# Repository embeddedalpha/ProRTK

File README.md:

# ProRTK 
Real Time Kinematic Board

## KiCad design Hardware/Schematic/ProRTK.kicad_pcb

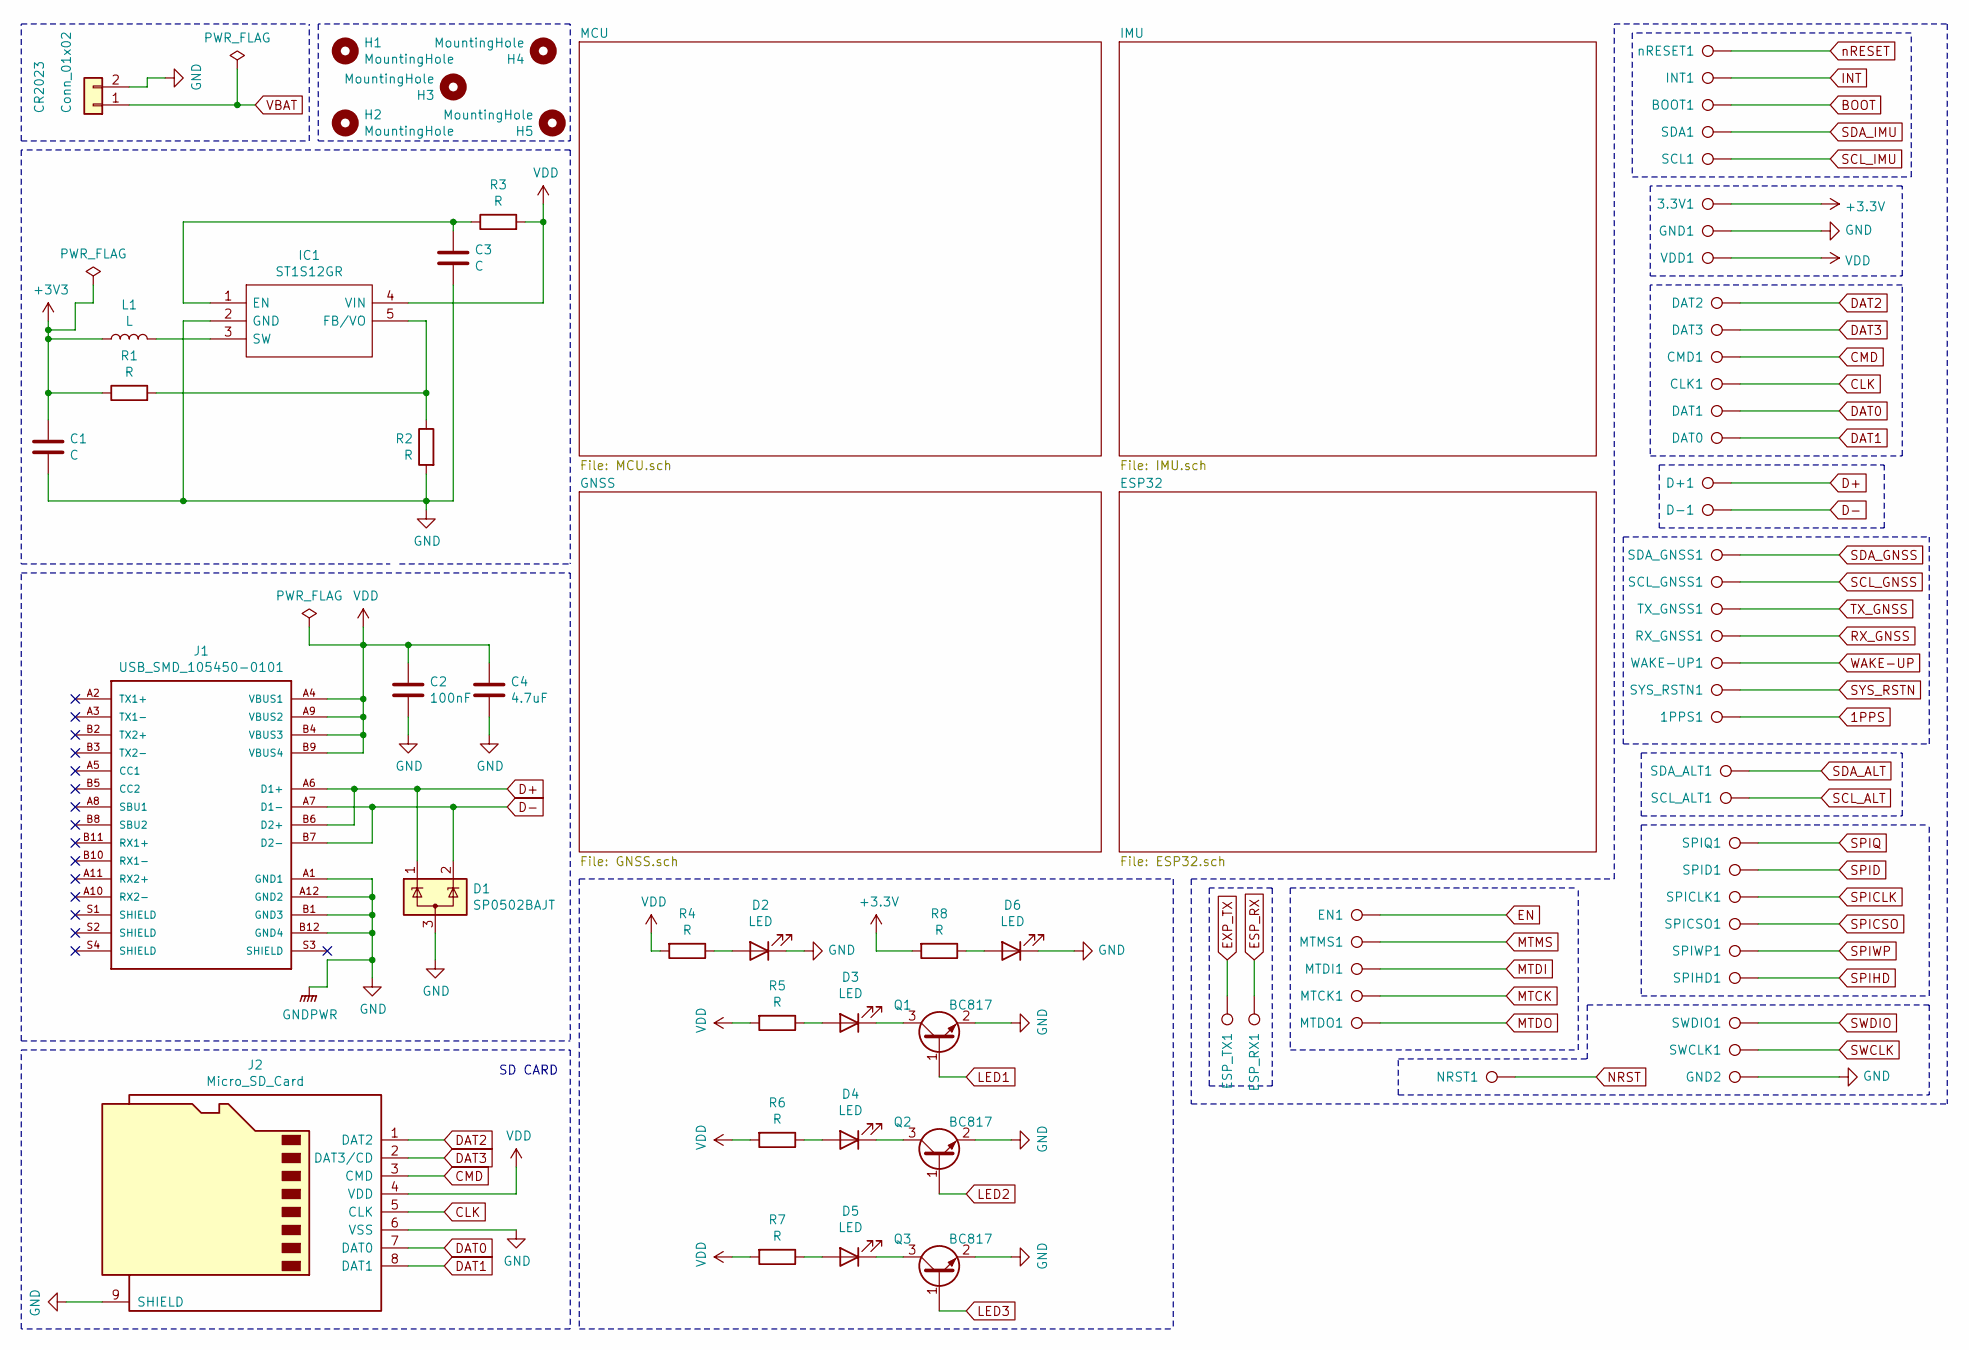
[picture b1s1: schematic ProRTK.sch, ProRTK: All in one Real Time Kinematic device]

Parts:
1PPS1, 3.3V1: TestPoint; testpoint_0.3mm
BOOT1: TestPoint; testpoint_0.3mm
C1, C3: C; C_0402_1005Metric
C2: 100nF; C_0402_1005Metric
C4: 4.7uF; C_0402_1005Metric
CLK1: TestPoint; testpoint_0.3mm
CMD1: TestPoint; testpoint_0.3mm
CR2023: Conn_01x02; BatteryHolder_Keystone_3034_1x20mm
D1: SP0502BAJT; SOT-323_SC-70
D2, D3, D4, D5, D6: LED; LED_0603_1608Metric
D+1: TestPoint; testpoint_0.3mm
D-1: TestPoint; testpoint_0.3mm
DAT0, DAT1, DAT2, DAT3: TestPoint; testpoint_0.3mm
EN1: TestPoint; testpoint_0.3mm
ESP_RX1: TestPoint; testpoint_0.3mm
ESP_TX1: TestPoint; testpoint_0.3mm
GND1, GND2: TestPoint; testpoint_0.3mm
H1, H2, H3, H4, H5: MountingHole; MountingHole_3.2mm_M3_Pad_Via
IC1: ST1S12GR; SOT95P280X110-5N; Mouser Part Number 511-ST1S12GR
INT1: TestPoint; testpoint_0.3mm
J1: USB_SMD_105450-0101; MOLEX_105450-0101
J2: Micro_SD_Card; microSD_HC_Hirose_DM3D-SF
L1: L; L_0402_1005Metric
MTCK1: TestPoint; testpoint_0.3mm
MTDI1: TestPoint; testpoint_0.3mm
MTDO1: TestPoint; testpoint_0.3mm
MTMS1: TestPoint; testpoint_0.3mm
NRST1: TestPoint; testpoint_0.3mm
Q1, Q2, Q3: BC817; SOT-23
R1, R2, R3, R4, R5, R6, R7, R8: R; R_0402_1005Metric
RX_GNSS1: TestPoint; testpoint_0.3mm
SCL1: TestPoint; testpoint_0.3mm
SCL_ALT1: TestPoint; testpoint_0.3mm
SCL_GNSS1: TestPoint; testpoint_0.3mm
SDA1: TestPoint; testpoint_0.3mm
SDA_ALT1: TestPoint; testpoint_0.3mm
SDA_GNSS1: TestPoint; testpoint_0.3mm
SPICLK1: TestPoint; testpoint_0.3mm
SPICSO1: TestPoint; testpoint_0.3mm
SPID1: TestPoint; testpoint_0.3mm
SPIHD1: TestPoint; testpoint_0.3mm
SPIQ1: TestPoint; testpoint_0.3mm
SPIWP1: TestPoint; testpoint_0.3mm
SWCLK1: TestPoint; testpoint_0.3mm
SWDIO1: TestPoint; testpoint_0.3mm
SYS_RSTN1: TestPoint; testpoint_0.3mm
TX_GNSS1: TestPoint; testpoint_0.3mm
VDD1: TestPoint; testpoint_0.3mm
WAKE-UP1: TestPoint; testpoint_0.3mm
nRESET1: TestPoint; testpoint_0.3mm

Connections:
1PPS: 1PPS1.1; also elsewhere on the board
BOOT: BOOT1.1; also elsewhere on the board
CLK: CLK1.1, J2.5 (CLK); also elsewhere on the board
CMD: CMD1.1, J2.3 (CMD); also elsewhere on the board
D+: D1.1 (K), D+1.1, J1.A6 (D1+), J1.B6 (D2+); also elsewhere on the board
D-: D1.2 (K), D-1.1, J1.A7 (D1-), J1.B7 (D2-); also elsewhere on the board
DAT0: DAT1.1, J2.7 (DAT0); also elsewhere on the board
DAT1: DAT0.1, J2.8 (DAT1); also elsewhere on the board
DAT2: DAT2.1, J2.1 (DAT2); also elsewhere on the board
DAT3: DAT3.1, J2.2 (DAT3/CD); also elsewhere on the board
EN: EN1.1; also elsewhere on the board
ESP_RX: ESP_RX1.1; also elsewhere on the board
EXP_TX: ESP_TX1.1; also elsewhere on the board
GND: C1.2, C2.2, C3.2, C4.2, CR2023.2, D1.3 (A), D2.1 (K), D6.1 (K), GND1.1, GND2.1, IC1.2 (GND), J1.A1 (GND1), J1.A12 (GND2), J1.B1 (GND3), J1.B12 (GND4), J2.6 (VSS), J2.9 (SHIELD), Q1.2 (E), Q2.2 (E), Q3.2 (E), R2.2; also elsewhere on the board
INT: INT1.1; also elsewhere on the board
LED1: Q1.1 (B); also elsewhere on the board
LED2: Q2.1 (B); also elsewhere on the board
LED3: Q3.1 (B); also elsewhere on the board
MTCK: MTCK1.1; also elsewhere on the board
MTDI: MTDI1.1; also elsewhere on the board
MTDO: MTDO1.1; also elsewhere on the board
MTMS: MTMS1.1; also elsewhere on the board
NRST: NRST1.1; also elsewhere on the board
unnamed: C3.1, IC1.1 (EN), R3.1
unnamed: D2.2 (A), R4.1
unnamed: D3.1 (K), Q1.3 (C)
unnamed: D3.2 (A), R5.1
unnamed: D4.1 (K), Q2.3 (C)
unnamed: D4.2 (A), R6.1
unnamed: D5.1 (K), Q3.3 (C)
unnamed: D5.2 (A), R7.1
unnamed: D6.2 (A), R8.1
unnamed: IC1.3 (SW), L1.2
unnamed: IC1.5 (FB/VO), R1.2, R2.1
RX_GNSS: RX_GNSS1.1; also elsewhere on the board
SCL_ALT: SCL1.1, SCL_ALT1.1; also elsewhere on the board
SCL_GNSS: SCL_GNSS1.1; also elsewhere on the board
SDA_ALT: SDA1.1, SDA_ALT1.1; also elsewhere on the board
SDA_GNSS: SDA_GNSS1.1; also elsewhere on the board
SPICLK: SPICLK1.1; also elsewhere on the board
SPICSO: SPICSO1.1; also elsewhere on the board
SPID: SPID1.1; also elsewhere on the board
SPIHD: SPIHD1.1; also elsewhere on the board
SPIQ: SPIQ1.1; also elsewhere on the board
SPIWP: SPIWP1.1; also elsewhere on the board
SWCLK: SWCLK1.1; also elsewhere on the board
SWDIO: SWDIO1.1; also elsewhere on the board
SYS_RSTN: SYS_RSTN1.1; also elsewhere on the board
TX_GNSS: TX_GNSS1.1; also elsewhere on the board
WAKE-UP: WAKE-UP1.1; also elsewhere on the board
nRESET: nRESET1.1; also elsewhere on the board

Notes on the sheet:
SD CARD

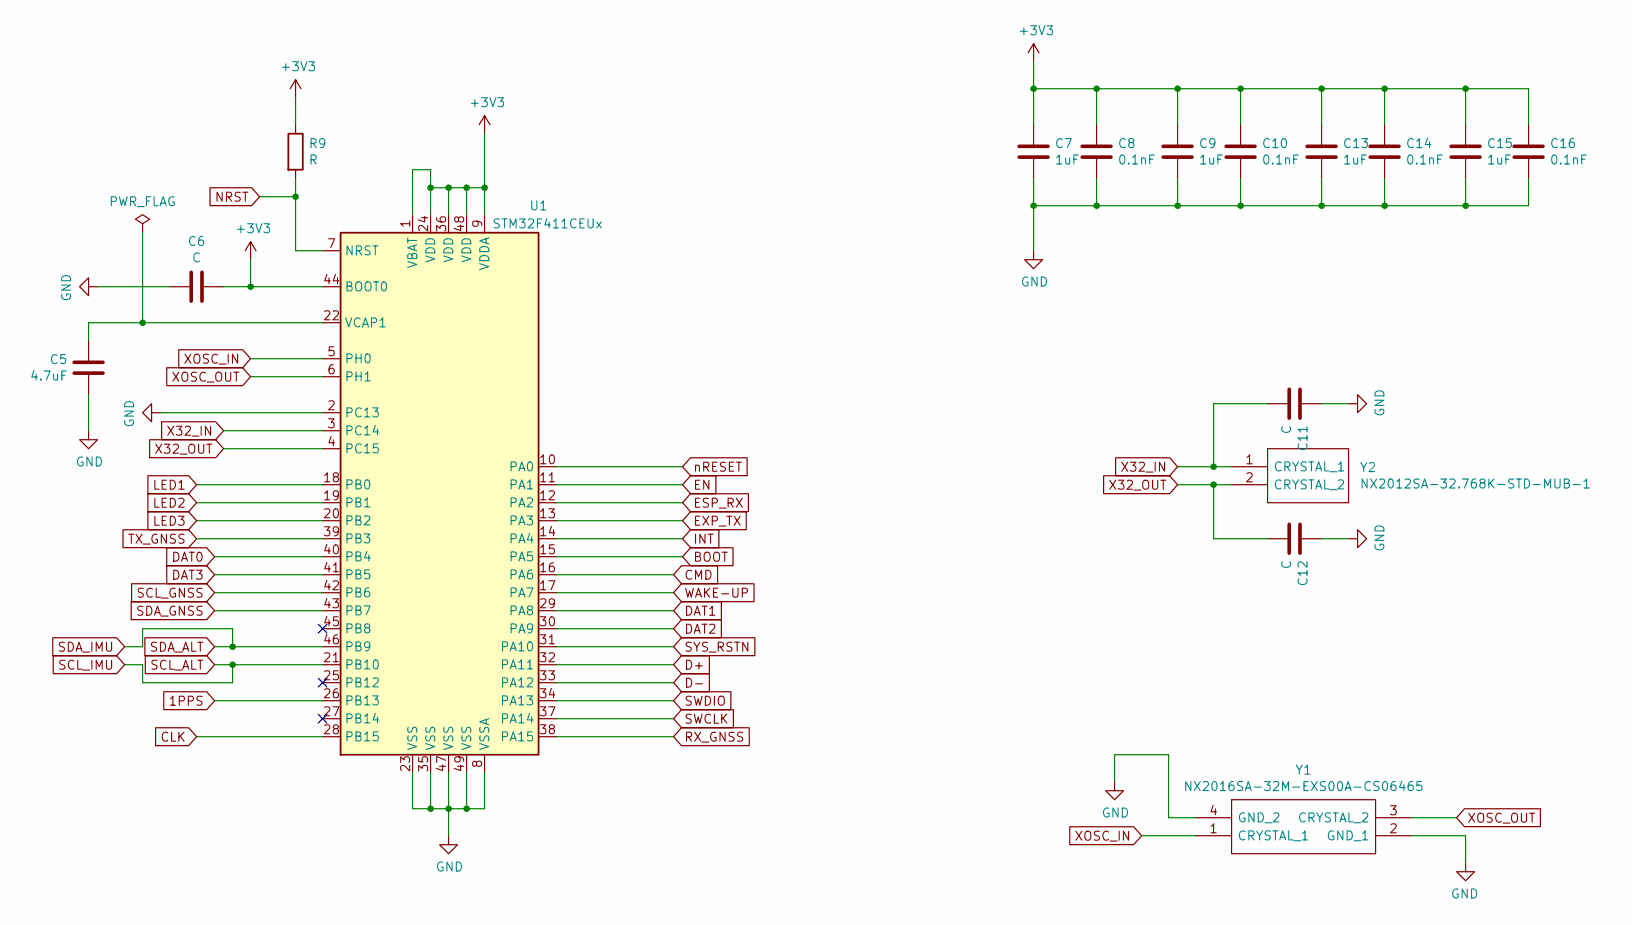
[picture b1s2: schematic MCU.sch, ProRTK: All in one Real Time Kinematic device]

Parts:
C5: 4.7uF; C_0402_1005Metric
C6, C11, C12: C; C_0402_1005Metric
C7, C9, C13, C15: 1uF; C_0402_1005Metric
C8, C10, C14, C16: 0.1nF; C_0402_1005Metric
R9: R; R_0402_1005Metric
U1: STM32F411CEUx; QFN-48-1EP_7x7mm_P0.5mm_EP5.6x5.6mm
Y1: NX2016SA-32M-EXS00A-CS06465; NX2016SA32MEXS00ACS06465; Mouser Part Number 344-NX2016SA32S06465
Y2: NX2012SA-32.768K-STD-MUB-1; NX2012SA32768KSTDMUB1; Mouser Part Number 344-NX2012SA32768K1

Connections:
1PPS: U1.26 (PB13); also elsewhere on the board
BOOT: U1.15 (PA5); also elsewhere on the board
CLK: U1.28 (PB15); also elsewhere on the board
CMD: U1.16 (PA6); also elsewhere on the board
D+: U1.32 (PA11); also elsewhere on the board
D-: U1.33 (PA12); also elsewhere on the board
DAT0: U1.40 (PB4); also elsewhere on the board
DAT1: U1.29 (PA8); also elsewhere on the board
DAT2: U1.30 (PA9); also elsewhere on the board
DAT3: U1.41 (PB5); also elsewhere on the board
EN: U1.11 (PA1); also elsewhere on the board
ESP_RX: U1.12 (PA2); also elsewhere on the board
EXP_TX: U1.13 (PA3); also elsewhere on the board
GND: C5.1, C6.2, C7.2, C8.2, C9.2, C10.2, C11.1, C12.1, C13.2, C14.2, C15.2, C16.2, U1.2 (PC13), U1.8 (VSSA), U1.23 (VSS), U1.35 (VSS), U1.47 (VSS), U1.49 (VSS), Y1.2 (GND_1), Y1.4 (GND_2); also elsewhere on the board
INT: U1.14 (PA4); also elsewhere on the board
LED1: U1.18 (PB0); also elsewhere on the board
LED2: U1.19 (PB1); also elsewhere on the board
LED3: U1.20 (PB2); also elsewhere on the board
NRST: R9.2, U1.7 (NRST); also elsewhere on the board
unnamed: C5.2, U1.22 (VCAP1)
RX_GNSS: U1.38 (PA15); also elsewhere on the board
SCL_ALT: U1.21 (PB10); also elsewhere on the board
SCL_GNSS: U1.42 (PB6); also elsewhere on the board
SDA_ALT: U1.46 (PB9); also elsewhere on the board
SDA_GNSS: U1.43 (PB7); also elsewhere on the board
SWCLK: U1.37 (PA14); also elsewhere on the board
SWDIO: U1.34 (PA13); also elsewhere on the board
SYS_RSTN: U1.31 (PA10); also elsewhere on the board
TX_GNSS: U1.39 (PB3); also elsewhere on the board
WAKE-UP: U1.17 (PA7); also elsewhere on the board
X32_IN: C11.2, U1.3 (PC14), Y2.1 (CRYSTAL_1)
X32_OUT: C12.2, U1.4 (PC15), Y2.2 (CRYSTAL_2)
XOSC_IN: U1.5 (PH0), Y1.1 (CRYSTAL_1)
XOSC_OUT: U1.6 (PH1), Y1.3 (CRYSTAL_2)
nRESET: U1.10 (PA0); also elsewhere on the board

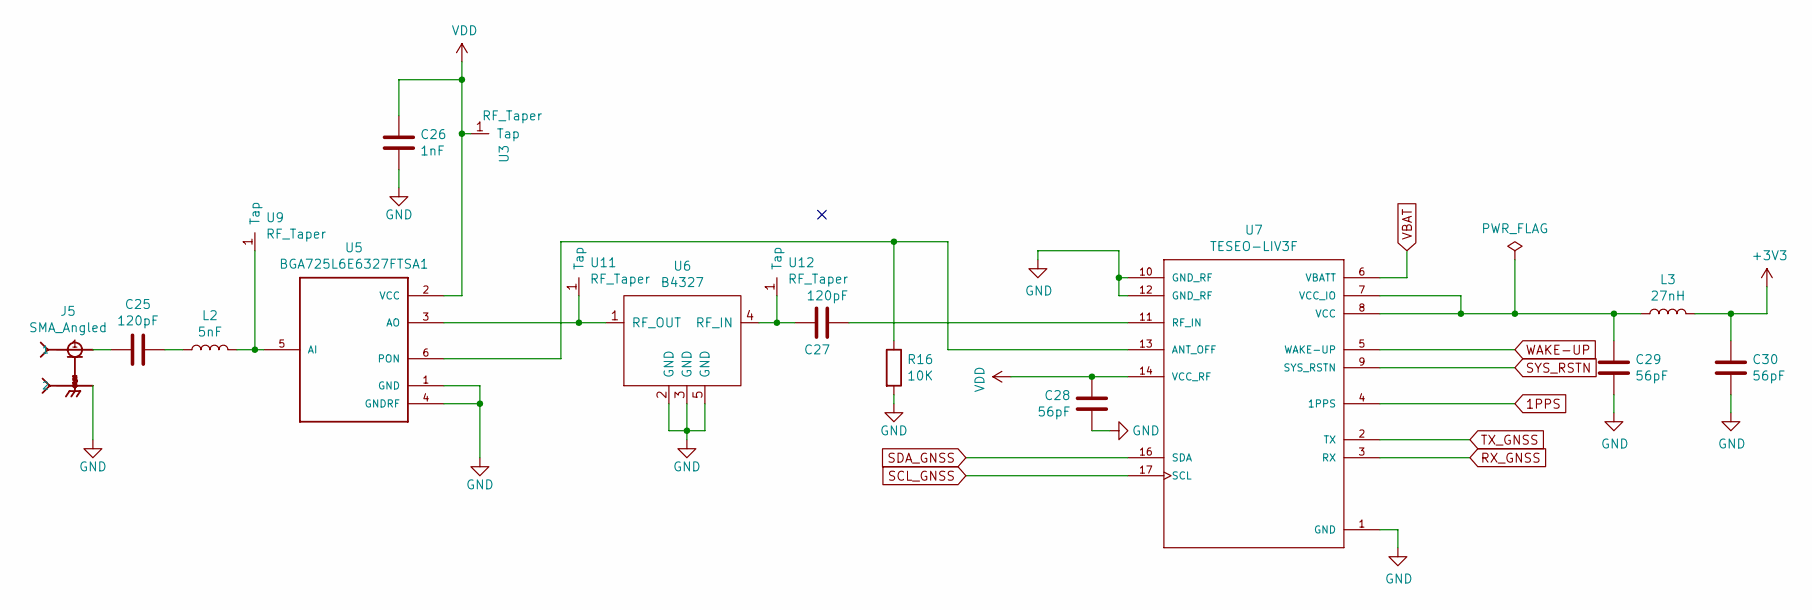
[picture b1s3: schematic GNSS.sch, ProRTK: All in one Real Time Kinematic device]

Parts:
C25, C27: 120pF; C_0402_1005Metric
C26: 1nF; C_0402_1005Metric
C28, C29, C30: 56pF; C_0402_1005Metric
J5: SMA_Angled; SMA_angled
L2: 5nF; L_0402_1005Metric
L3: 27nH; L_0402_1005Metric
R16: 10K; R_0402_1005Metric
U3, U9, U11, U12: RF_Taper; KL_Taper
U5: BGA725L6E6327FTSA1; BGA725L6E6327
U6: B4327
U7: TESEO-LIV3F

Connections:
1PPS: U7.4 (1PPS); also elsewhere on the board
GND: C26.2, C28.2, C29.2, C30.2, J5.2, J5.3 (2), J5.4 (2), J5.5 (2), R16.2, U5.1 (GND), U5.4 (GNDRF), U6.2 (GND), U6.3 (GND), U6.5 (GND), U7.1 (GND), U7.10 (GND_RF), U7.12 (GND_RF); also elsewhere on the board
unnamed: C25.1, L2.1
unnamed: C25.2, J5.1
unnamed: C27.1, U6.4 (RF_IN), U12.1
unnamed: C27.2, U7.11 (RF_IN)
unnamed: L2.2, U5.5 (AI), U9.1
unnamed: R16.1, U5.6 (PON), U7.13 (ANT_OFF)
unnamed: U5.3 (AO), U6.1 (RF_OUT), U11.1
RX_GNSS: U7.3 (RX); also elsewhere on the board
SCL_GNSS: U7.17 (SCL); also elsewhere on the board
SDA_GNSS: U7.16 (SDA); also elsewhere on the board
SYS_RSTN: U7.9 (SYS_RSTN); also elsewhere on the board
TX_GNSS: U7.2 (TX); also elsewhere on the board
VCC_RF: C26.1, C28.1, U3.1, U5.2 (VCC), U7.14 (VCC_RF)
WAKE-UP: U7.5 (WAKE-UP); also elsewhere on the board

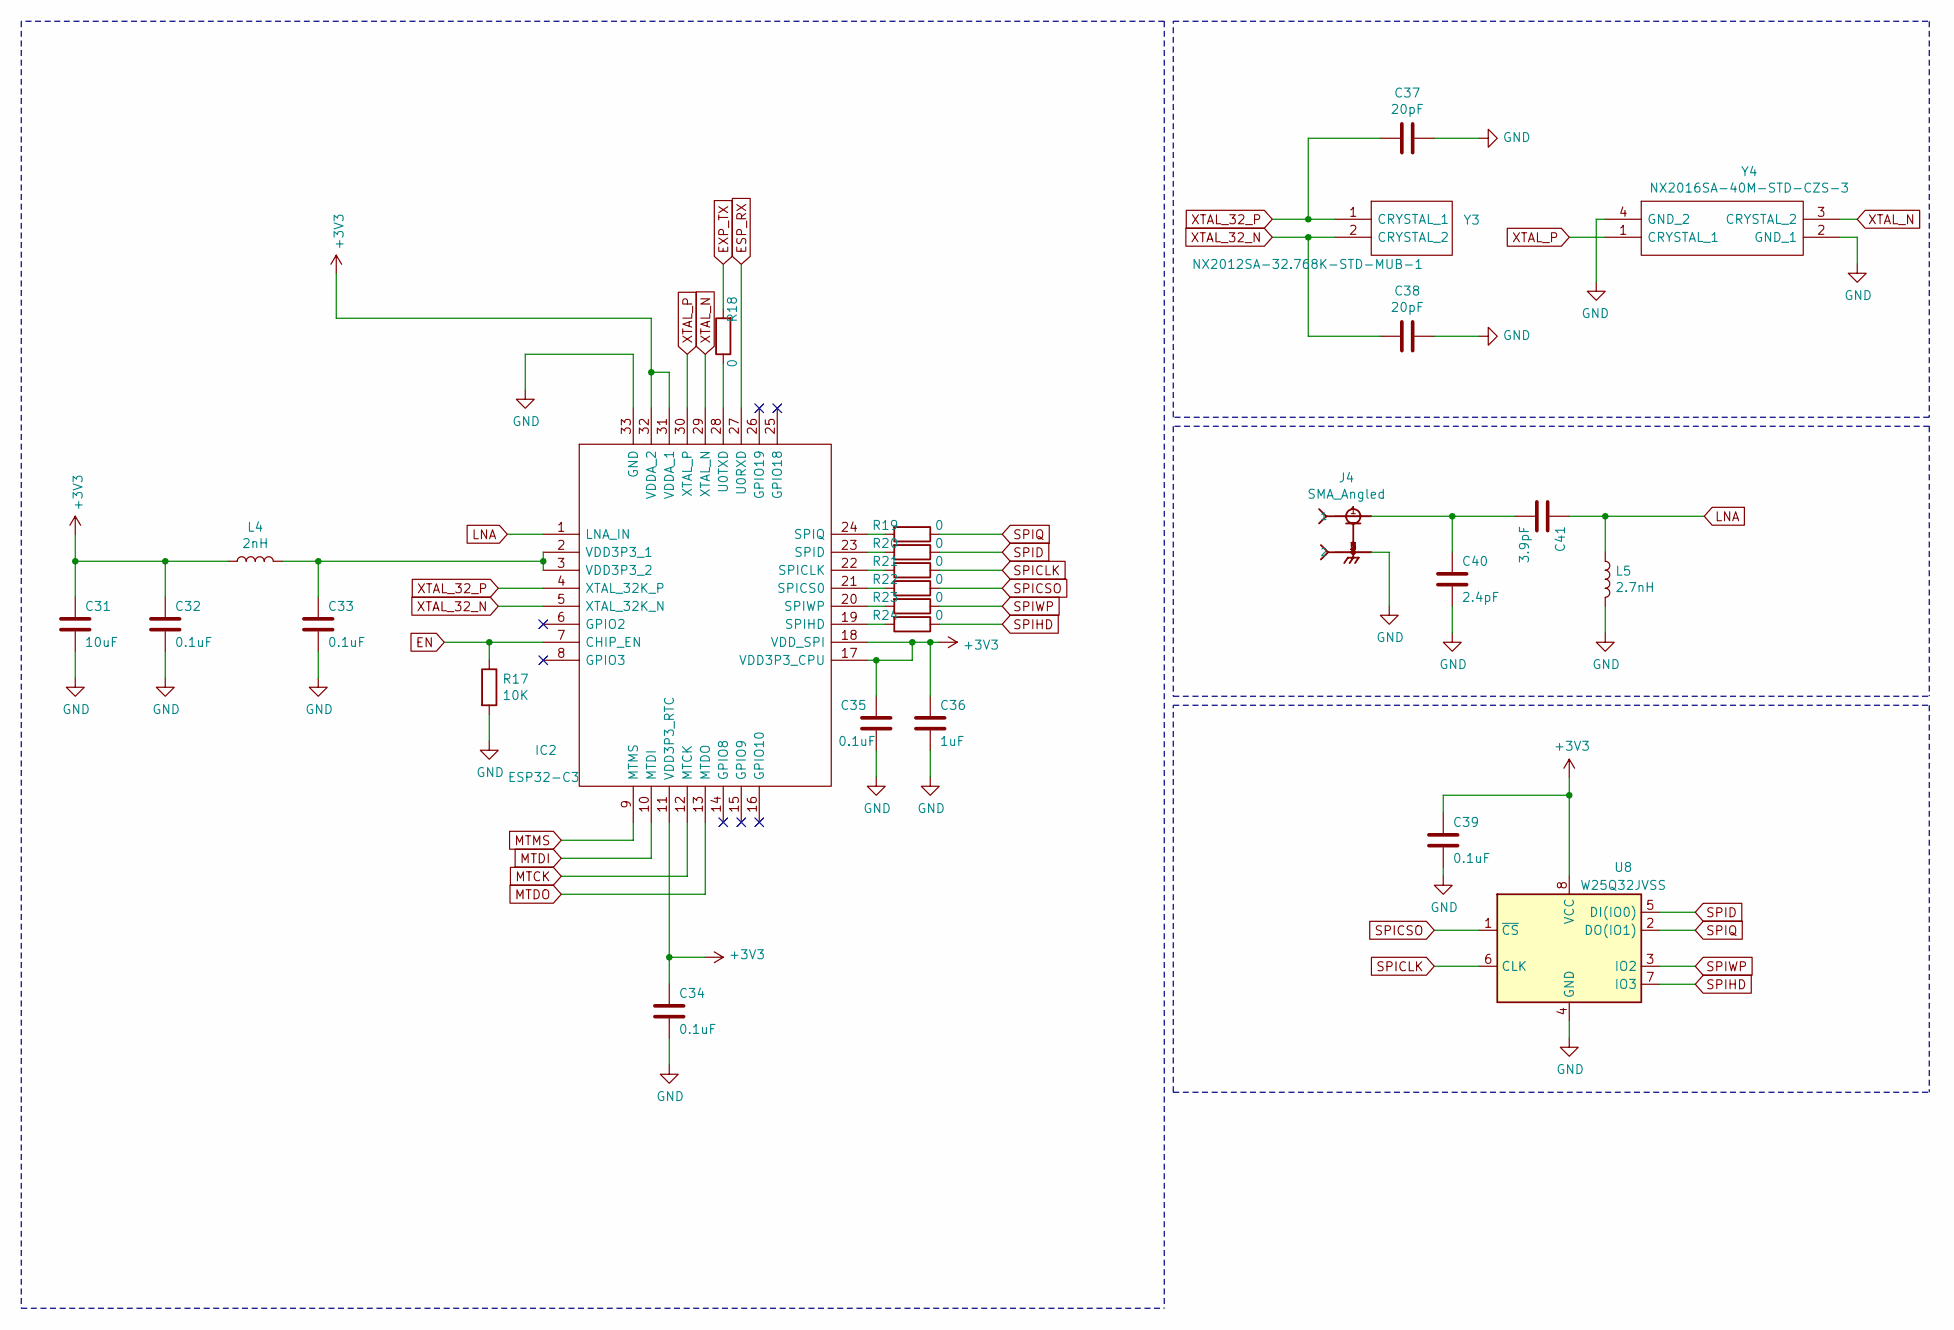
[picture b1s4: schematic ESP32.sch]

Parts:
C31: 10uF; C_0402_1005Metric
C32, C33, C34, C35, C39: 0.1uF; C_0402_1005Metric
C36: 1uF; C_0402_1005Metric
C37, C38: 20pF; C_0402_1005Metric
C40: 2.4pF; C_0402_1005Metric
C41: 3.9pF; C_0402_1005Metric
IC2: ESP32-C3; QFN50P500X500X90-33N-D; Manufacturer_Part_Number ESP32-C3
J4: SMA_Angled; SMA_angled
L4: 2nH; L_0402_1005Metric
L5: 2.7nH; L_0402_1005Metric
R17: 10K; R_0402_1005Metric
R18, R19, R20, R21, R22, R23, R24: 0; R_0402_1005Metric
U8: W25Q32JVSS; SOIC-8_5.23x5.23mm_P1.27mm
Y3: NX2012SA-32.768K-STD-MUB-1; NX2012SA32768KSTDMUB1; Mouser Part Number 344-NX2012SA32768K1
Y4: NX2016SA-40M-STD-CZS-3; NX2016SA40MSTDCZS3; Mouser Part Number 344-NX2016SA40MSTZS3

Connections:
EN: IC2.7 (CHIP_EN), R17.1; also elsewhere on the board
ESP_RX: IC2.27 (U0RXD); also elsewhere on the board
EXP_TX: R18.2; also elsewhere on the board
GND: C31.2, C32.2, C33.2, C34.2, C35.2, C36.2, C37.1, C38.1, C39.2, C40.2, IC2.33 (GND), J4.2, J4.3 (2), J4.4 (2), J4.5 (2), L5.2, R17.2, U8.4 (GND), Y4.2 (GND_1), Y4.4 (GND_2); also elsewhere on the board
LNA: C41.1, IC2.1 (LNA_IN), L5.1
MTCK: IC2.12 (MTCK); also elsewhere on the board
MTDI: IC2.10 (MTDI); also elsewhere on the board
MTDO: IC2.13 (MTDO); also elsewhere on the board
MTMS: IC2.9 (MTMS); also elsewhere on the board
unnamed: C33.1, IC2.2 (VDD3P3_1), IC2.3 (VDD3P3_2), L4.2
unnamed: C40.1, C41.2, J4.1
unnamed: IC2.19 (SPIHD), R24.2
unnamed: IC2.20 (SPIWP), R23.2
unnamed: IC2.21 (SPICS0), R22.2
unnamed: IC2.22 (SPICLK), R21.2
unnamed: IC2.23 (SPID), R20.2
unnamed: IC2.24 (SPIQ), R19.2
unnamed: IC2.28 (U0TXD), R18.1
SPICLK: R21.1, U8.6 (CLK); also elsewhere on the board
SPICSO: R22.1, U8.1 (~CS); also elsewhere on the board
SPID: R20.1, U8.5 (DI(IO0)); also elsewhere on the board
SPIHD: R24.1, U8.7 (IO3); also elsewhere on the board
SPIQ: R19.1, U8.2 (DO(IO1)); also elsewhere on the board
SPIWP: R23.1, U8.3 (IO2); also elsewhere on the board
XTAL_32_N: C38.2, IC2.5 (XTAL_32K_N), Y3.2 (CRYSTAL_2)
XTAL_32_P: C37.2, IC2.4 (XTAL_32K_P), Y3.1 (CRYSTAL_1)
XTAL_N: IC2.29 (XTAL_N), Y4.3 (CRYSTAL_2)
XTAL_P: IC2.30 (XTAL_P), Y4.1 (CRYSTAL_1)

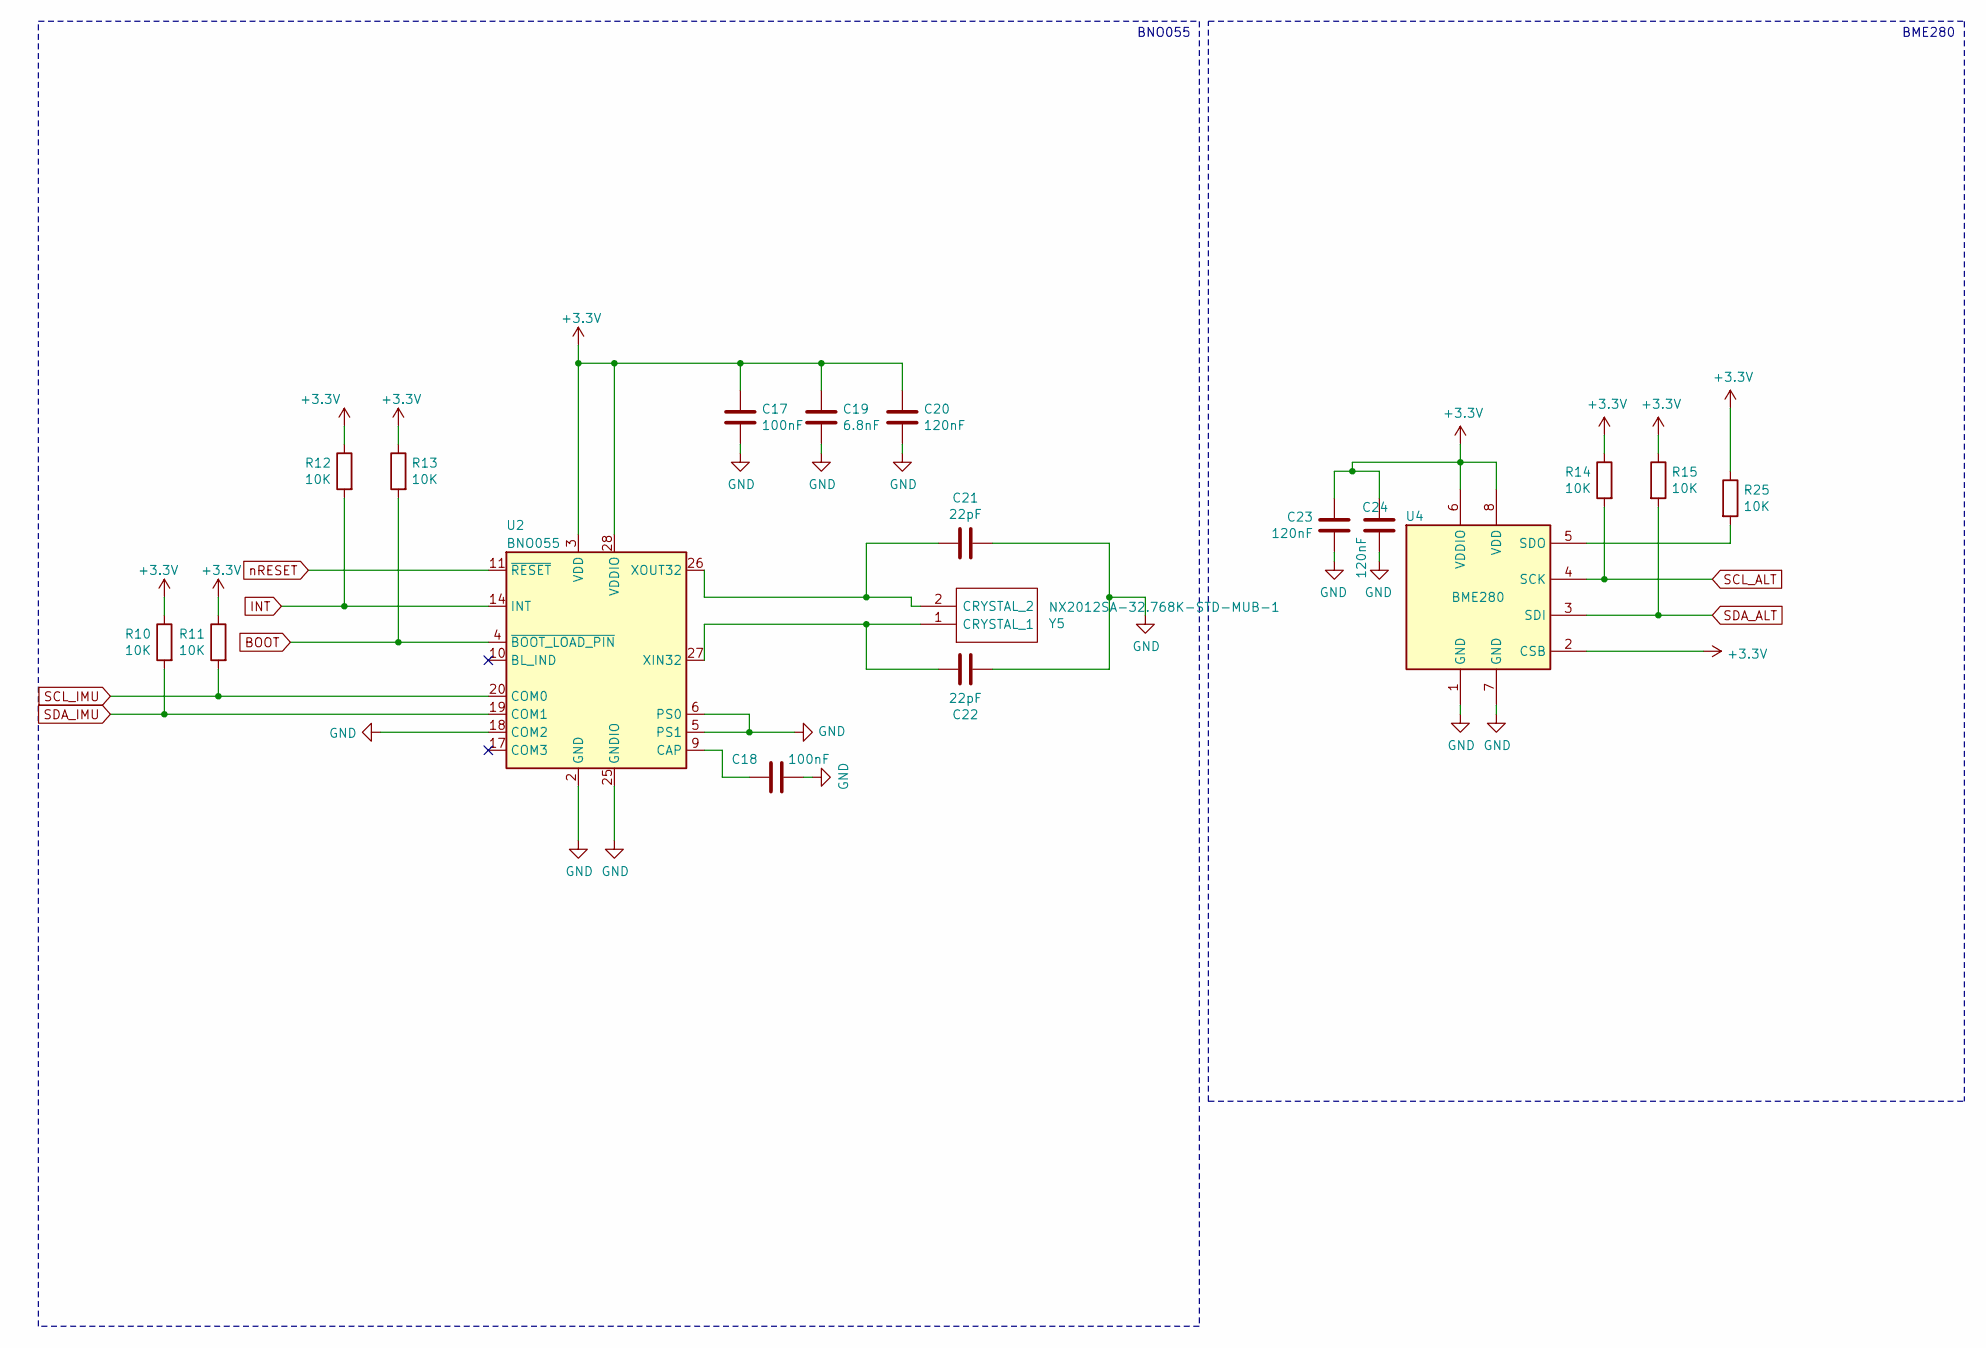
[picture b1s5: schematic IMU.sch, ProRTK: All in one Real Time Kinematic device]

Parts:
C17, C18: 100nF; C_0402_1005Metric
C19: 6.8nF; C_0402_1005Metric
C20, C23, C24: 120nF; C_0402_1005Metric
C21, C22: 22pF; C_0402_1005Metric
R10, R11, R12, R13, R14, R15, R25: 10K; R_0402_1005Metric
U2: BNO055; LGA-28_5.2x3.8mm_P0.5mm
U4: BME280; Bosch_LGA-8_2.5x2.5mm_P0.65mm_ClockwisePinNumbering
Y5: NX2012SA-32.768K-STD-MUB-1; NX2012SA32768KSTDMUB1; Mouser Part Number 344-NX2012SA32768K1

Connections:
BOOT: R13.2, U2.4 (~BOOT_LOAD_PIN); also elsewhere on the board
GND: C17.2, C18.2, C19.2, C20.2, C21.1, C22.1, C23.2, C24.2, U2.2 (GND), U2.5 (PS1), U2.6 (PS0), U2.15 (GNDIO), U2.16 (GNDIO), U2.18 (COM2), U2.25 (GNDIO), U4.1 (GND), U4.7 (GND); also elsewhere on the board
INT: R12.2, U2.14 (INT); also elsewhere on the board
unnamed: C18.1, U2.9 (CAP)
unnamed: C21.2, U2.26 (XOUT32), Y5.2 (CRYSTAL_2)
unnamed: C22.2, U2.27 (XIN32), Y5.1 (CRYSTAL_1)
unnamed: R25.2, U4.5 (SDO)
SCL_ALT: R11.2, R14.2, U2.20 (COM0), U4.4 (SCK); also elsewhere on the board
SDA_ALT: R10.2, R15.2, U2.19 (COM1), U4.3 (SDI); also elsewhere on the board
nRESET: U2.11 (~RESET); also elsewhere on the board

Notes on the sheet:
BNO055
BME280

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
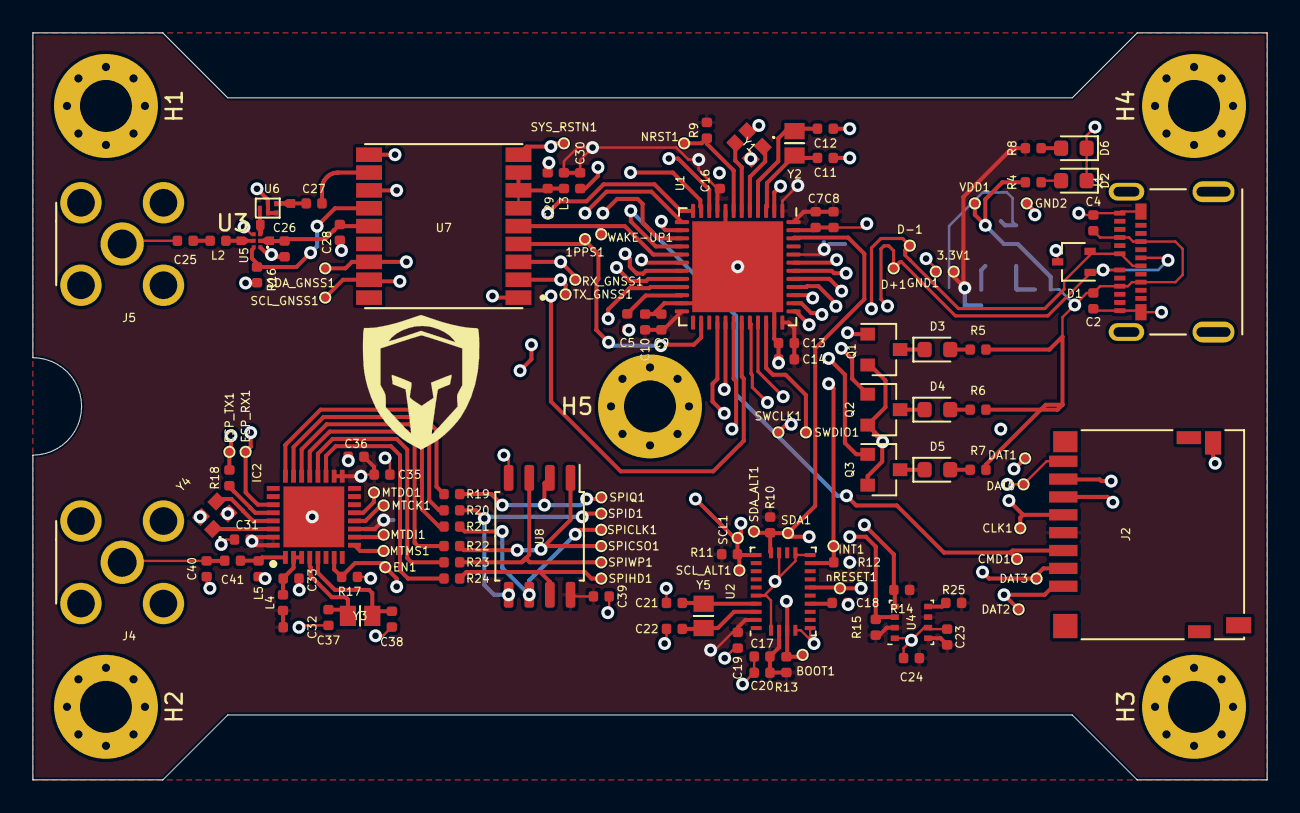
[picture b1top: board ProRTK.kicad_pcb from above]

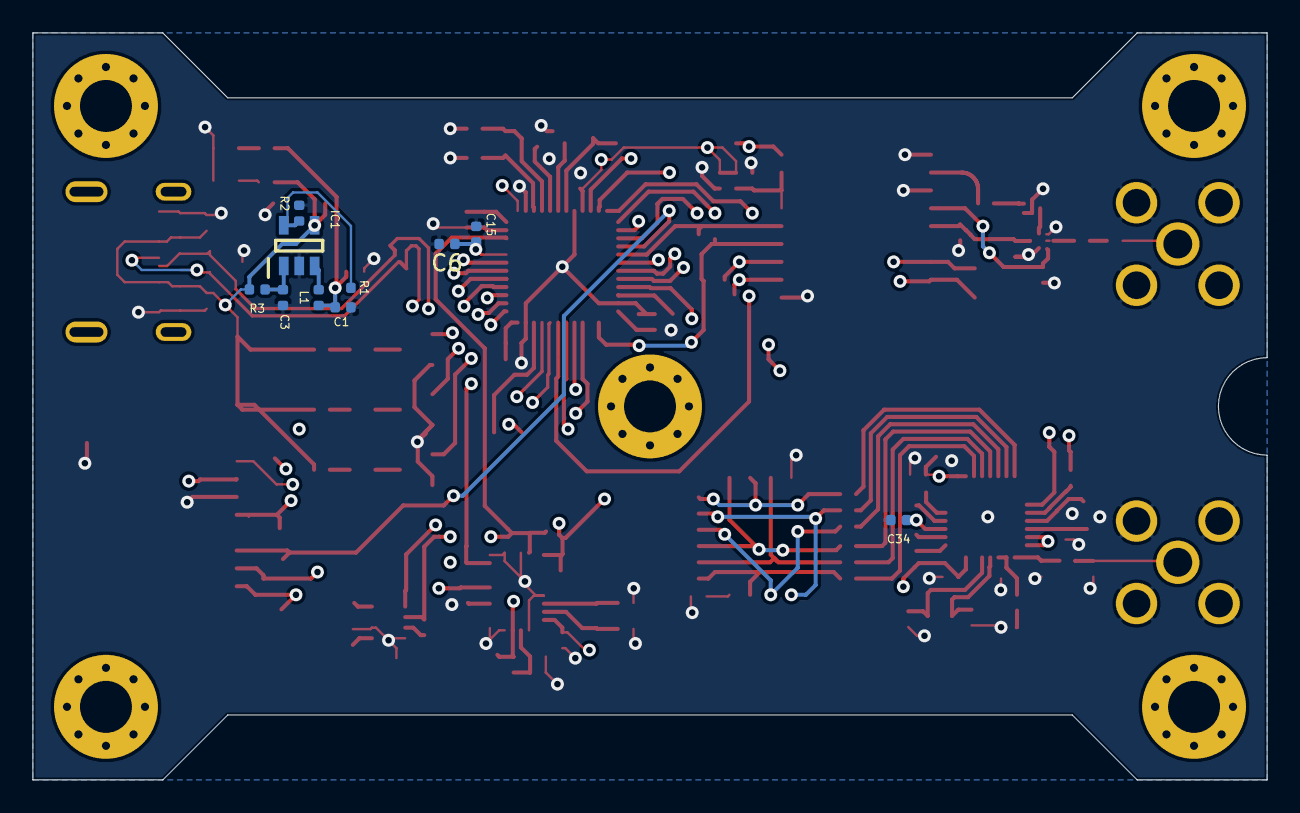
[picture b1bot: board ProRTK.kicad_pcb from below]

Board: 4 copper layers, 76.0 x 46.0 mm, 150 parts (10 on the bottom side), 85 nets.

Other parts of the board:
J3: Conn_01x01; Company_Logo1

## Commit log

2021-05-10 Create txt
2021-05-10 Create DXF
